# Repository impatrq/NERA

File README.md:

# N.E.R.A.

**Neuro Estimulación y Relajación Asistida**

Somos estudiantes de 7.º año de Aviónica de la **Escuela de Educación Secundaria Técnica N.º 7 «Taller Regional Quilmes» (IMPA)**. Durante 2026 desarrollamos NERA, un proyecto que combina investigación, electrónica, programación y diseño 3D.

[Repositorio oficial](https://github.com/impatrq/NERA) · [Seguimiento en Trello](https://trello.com/b/I9nTunkC/kanban-2026722cnera)

## ¿Qué es NERA?

NERA surgió con la idea de desarrollar una herramienta tecnológica que pueda acompañar a personas en situaciones de estrés o ansiedad. Construimos un prototipo portátil con **dos dispositivos principales: un reloj y una vincha**. Una aplicación móvil complementa el sistema y permite consultar las mediciones.

También investigamos los campos electromagnéticos pulsados (**PEMF**) de baja frecuencia y sus posibles aplicaciones. Esta parte sigue siendo experimental: todavía no demostramos efectos terapéuticos ni validamos la seguridad del dispositivo para su aplicación sobre personas.

## ¿Cómo funciona?

El **reloj** utiliza un ESP32-S3 para recopilar información de los sensores, procesarla y mostrarla en su pantalla táctil. Mediante **Bluetooth Low Energy (BLE)** envía lecturas a la aplicación móvil, donde se pueden consultar datos, historial y preferencias.

El reloj también se comunica con la **vincha**, controlada por un ESP32-C3, mediante **ESP-NOW**. Probamos el intercambio de mensajes, alertas de laboratorio y confirmaciones de recepción. La vincha contiene bobinas y una electrónica de control; el accionamiento seguro y automático de las bobinas a partir de las mediciones todavía requiere validación eléctrica.

## Prototipos reales

Estas son las versiones físicas del reloj y la vincha que construimos, ajustamos y presentamos durante el desarrollo del proyecto.

| Reloj NERA | Vincha NERA |
|:---:|:---:|
|  |  |
| **Reloj con carcasa impresa en 3D** | **Vincha con las carcasas de las bobinas** |

## Modelos actuales en CAD

Estos son algunos de los diseños actuales de la estructura del reloj y de la vincha hechos para adaptar el prototipo a los componentes reales.

| Modelo del reloj | Modelo de la vincha |
|:---:|:---:|
|  |  |
| **Carcasa del reloj** | **Soporte de la vincha y bobina** |

## PCB y proceso electrónico

Durante el proyecto diseñamos placas, corregimos pistas, soldamos componentes y probamos módulos reales para verificar conexiones y funcionamiento.

| Diseño PCB | Placa en pruebas |
|:---:|:---:|
|  |  |
| **Diseño de la PCB** | **Placa de sensores armada** |

## Componentes del sistema

### Reloj inteligente

El reloj utiliza un **ESP32-S3** con pantalla táctil de **240 × 320 píxeles**. El firmware se desarrolló con **C/C++, ESP-IDF, FreeRTOS y LVGL**.

| Componente | Función |
| --- | --- |
| **ESP32-S3** | Procesamiento, pantalla y comunicaciones inalámbricas. |
| **MAX30102** | Señal óptica para estimar frecuencia cardíaca y SpO₂. |
| **MLX90614** | Medición infrarroja de temperatura de objeto. |
| **MPU6050** | Registro de movimiento mediante acelerómetro y giroscopio. |

Las estimaciones de pulso y SpO₂ dependen de lecturas válidas. La temperatura infrarroja registrada no representa directamente la temperatura corporal central.

[Ver firmware del reloj](firmware/Codigo%20Reloj/) · [Guía técnica](firmware/Codigo%20Reloj/LEER_PRIMERO.md)

### Vincha experimental

La vincha incorpora un **ESP32-C3**, una placa controladora, una etapa de potencia y bobinas realizadas con cobre esmaltado. Diseñamos y fabricamos distintas versiones de las carcasas para montar los componentes.

Investigamos frecuencias entre **10 y 30 Hz**. El firmware publicado contiene una prueba de señal a **15 Hz con las bobinas desconectadas**. Esta prueba permite comprobar la salida eléctrica, pero no demuestra la seguridad ni la eficacia de la estimulación.

[Ver firmware de la vincha](firmware/Codigo%20Vincha/) · [Documentación de la prueba de 15 Hz](firmware/Codigo%20Vincha/docs/PRUEBA_GPIO5_15HZ.md)

### Aplicación móvil

La aplicación fue desarrollada con **Flutter y Dart**. Cuenta con las secciones **Inicio, Salud, Apoyo y Perfil**. Permite consultar mediciones e historial del reloj por BLE, configurar preferencias y utilizar funciones de respiración. La red de apoyo está contemplada en la interfaz; el envío automático de avisos a contactos todavía no se encuentra implementado.

[Ver aplicación](firmware/Codigo%20Aplicacion/) · [Mapa del código](firmware/Codigo%20Aplicacion/GUIA_CODIGO.md)

| Pantalla de inicio | Consulta de mediciones |
| :---: | :---: |
|  |  |
| **Inicio** | **Salud** |

## Presupuesto estimado

El costo estimado de los materiales electrónicos relevados es de **$156.978,12 ARS**. Son **precios de referencia**, no gastos efectivamente comprobados.

| Componente | Cantidad | Subtotal (ARS) |
| --- | :---: | ---: |
| ESP32-S3 + pantalla | 1 | $48.510 |
| ESP32-C3 SuperMini | 1 | $7.999 |
| MAX30102 | 1 | $7.860 |
| MLX90614 | 1 | $24.459 |
| MPU6050 | 1 | $6.149 |
| MOSFET IRFZ44N | 2 | $4.398 |
| TP4056 (módulo) | 1 | $3.499 |
| Baterías 18650 | 2 | $9.213,16 |
| Baterías LQ-S1 (pack de 2) | 1 | $14.418,97 |
| Cobre esmaltado (250 g) | 1 | $19.123,99 |
| LM2596 | 1 | $4.999 |
| Portabaterías | 1 | $6.349 |
| **Total estimado** |  | **$156.978,12** |

Este valor **no incluye** fabricación de PCB, resistencias, capacitores, diodos, cables, impresión 3D, tornillos ni otros materiales. Algunas cantidades fueron estimadas a partir de los circuitos y no está confirmado que se hayan comprado todos los elementos de la lista.

## Avances y estado actual

A lo largo del año fabricamos y probamos las placas y carcasas, desarrollamos la interfaz del reloj e integramos la aplicación. Las pruebas documentadas incluyen comunicación **BLE** entre el reloj y el teléfono, sincronización e historial de mediciones y comunicación **ESP-NOW** entre los dos microcontroladores.

El prototipo sigue en desarrollo. Quedan pendientes ajustes en la alimentación, estabilidad de sensores, validación del circuito de potencia y funcionamiento integrado. La activación mediante combinación de variables es una idea de evolución del sistema; en el firmware documentado actualmente se usan reglas de laboratorio independientes para pulso y temperatura. **NERA no es un sistema médico validado para diagnosticar o tratar estrés o ansiedad.**

## Integrantes

| Integrante | Área principal |
| --- | --- |
| **Erik Kriznjak** | Programación del reloj, aplicación móvil, comunicaciones e integración. |
| **Juan Cruz Beneitez** | Electrónica, sensores, PCB, soldadura y pruebas de los circuitos. |
| **Ignacio Villegas** | Diseño CAD, impresión 3D, carcasas y armado de los dispositivos. |
| **Enzo Segovia** | Investigación de componentes, parámetros fisiológicos y tecnología PEMF. |

Los cuatro participamos en las pruebas, correcciones y exposición del prototipo.

## Archivos del proyecto

| Carpeta | Contenido |
| --- | --- |
| [`circuitos/`](circuitos/) | Esquemáticos y diseños de placas PCB. |
| [`mechanical/`](mechanical/) | Modelos 3D, carcasas y archivos STL de fabricación. |
| [`firmware/`](firmware/) | Código del reloj, la vincha y la aplicación móvil. |
| [`docs/`](docs/) | Manuales, documentación técnica e imágenes. |

Para acceder al código y a sus instrucciones de compilación: [README de firmware](firmware/README.md).

---

**Proyecto NERA · 7.º año de Aviónica · E.E.S.T. N.º 7 · Quilmes · 2026**

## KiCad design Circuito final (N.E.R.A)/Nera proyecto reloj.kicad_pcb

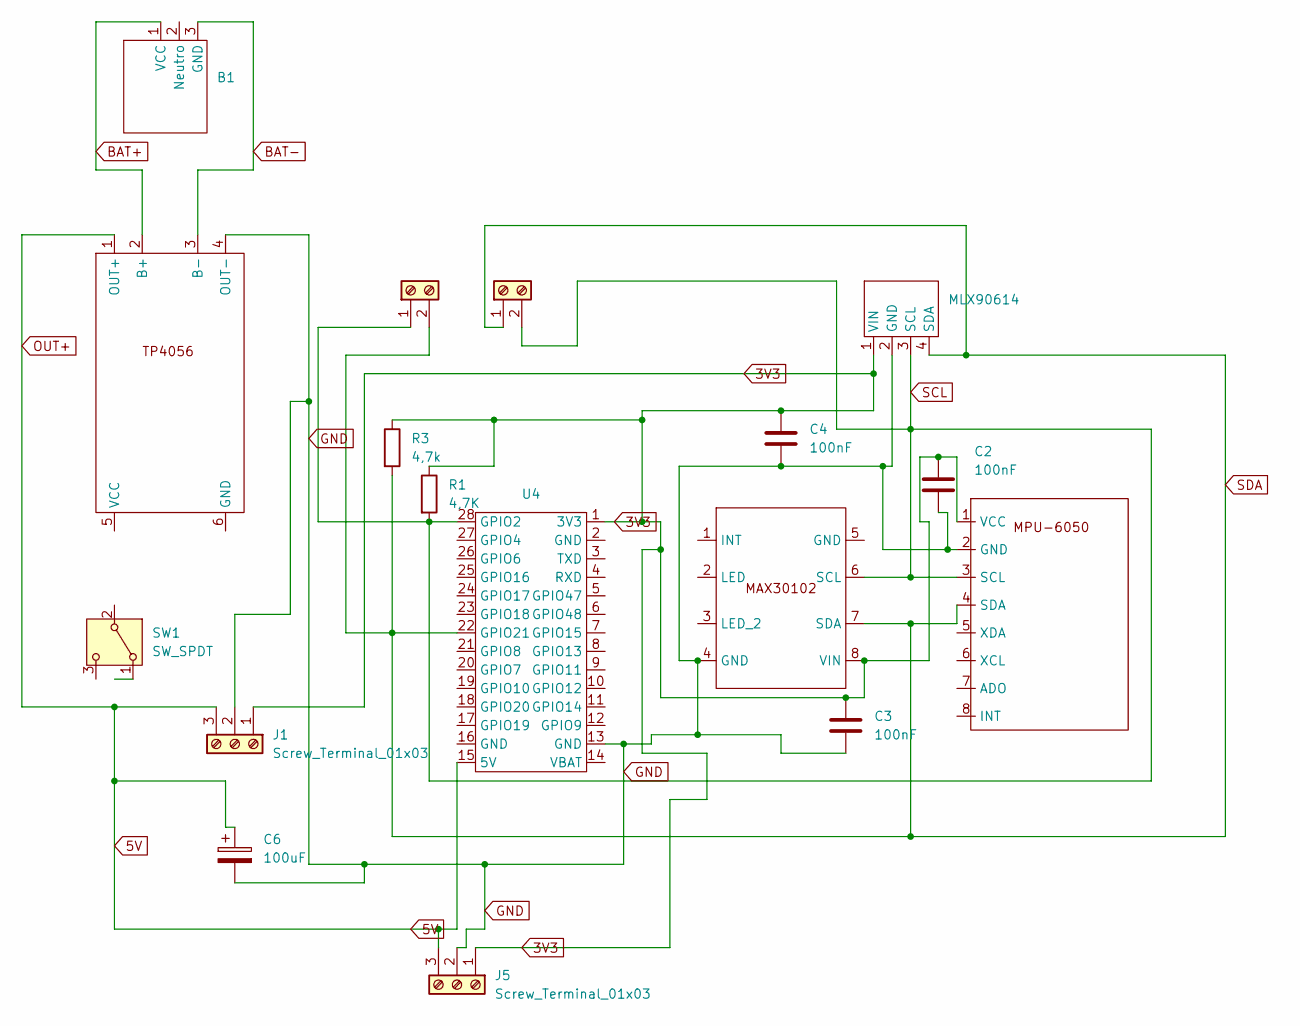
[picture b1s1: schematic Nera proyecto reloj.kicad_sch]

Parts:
B1: batman 51
C2, C3, C4: 100nF; C_Radial_D4.0mm_H5.0mm_P1.50mm
C6: 100uF; CP_Radial_D5.0mm_P2.00mm
J1, J5: Screw_Terminal_01x03; TerminalBlock_MaiXu_MX126-5.0-03P_1x03_P5.00mm
J3: TerminalBlock:TerminalBlock_MaiXu_MX126-5.0-02P_1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; TerminalBlock_MaiXu_MX126-5.0-02P_1x02_P5.00mm
J4: Screw_Terminal_01x02; TerminalBlock_MaiXu_MX126-5.0-02P_1x02_P5.00mm
MLX90614: MLX90614
Max1: MAX30102; Max 30102
R1: 4,7K; R_Axial_DIN0411_L9.9mm_D3.6mm_P15.24mm_Horizontal
R3: 4,7k; R_Axial_DIN0411_L9.9mm_D3.6mm_P15.24mm_Horizontal
SW1: SW_SPDT; SW_Slide_SPDT_Straight_CK_OS102011MS2Q
TP1: TP4056-42-ESOP8; Modulito
U2: MPU-6050; MPU 6050
U4: esp32 s3

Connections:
3V3: C2.1, C3.1, C4.1, J1.1, J5.1, MLX90614.1 (VIN), Max1.8 (VIN), R1.1, R3.1, U2.1 (VCC), U4.1 (3V3)
5V: C6.1, J1.3, J5.3, TP1.1 (OUT+), U4.15 (5V)
BAT+: B1.1 (VCC), TP1.2 (B+)
BAT-: B1.3 (GND), TP1.3 (B-)
GND: C2.2, C3.2, C4.2, C6.2, J1.2, J5.2, MLX90614.2 (GND), Max1.4 (GND), TP1.4 (OUT-), U2.2 (GND), U4.13 (GND)
SCL: J3.1, J4.2, MLX90614.3 (SCL), Max1.6 (SCL), R1.2, U2.3 (SCL), U4.28 (GPIO2)
SDA: J3.2, J4.1, MLX90614.4 (SDA), Max1.7 (SDA), R3.2, U2.4 (SDA), U4.22 (GPIO21)

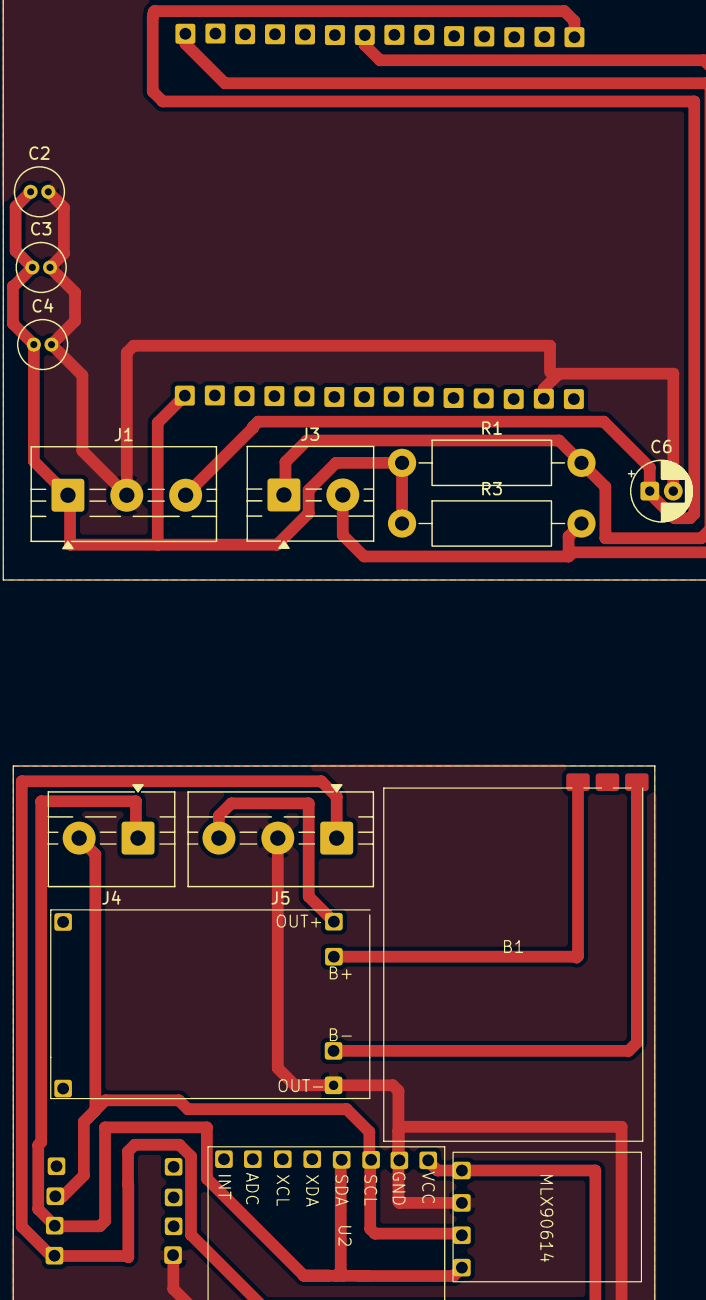
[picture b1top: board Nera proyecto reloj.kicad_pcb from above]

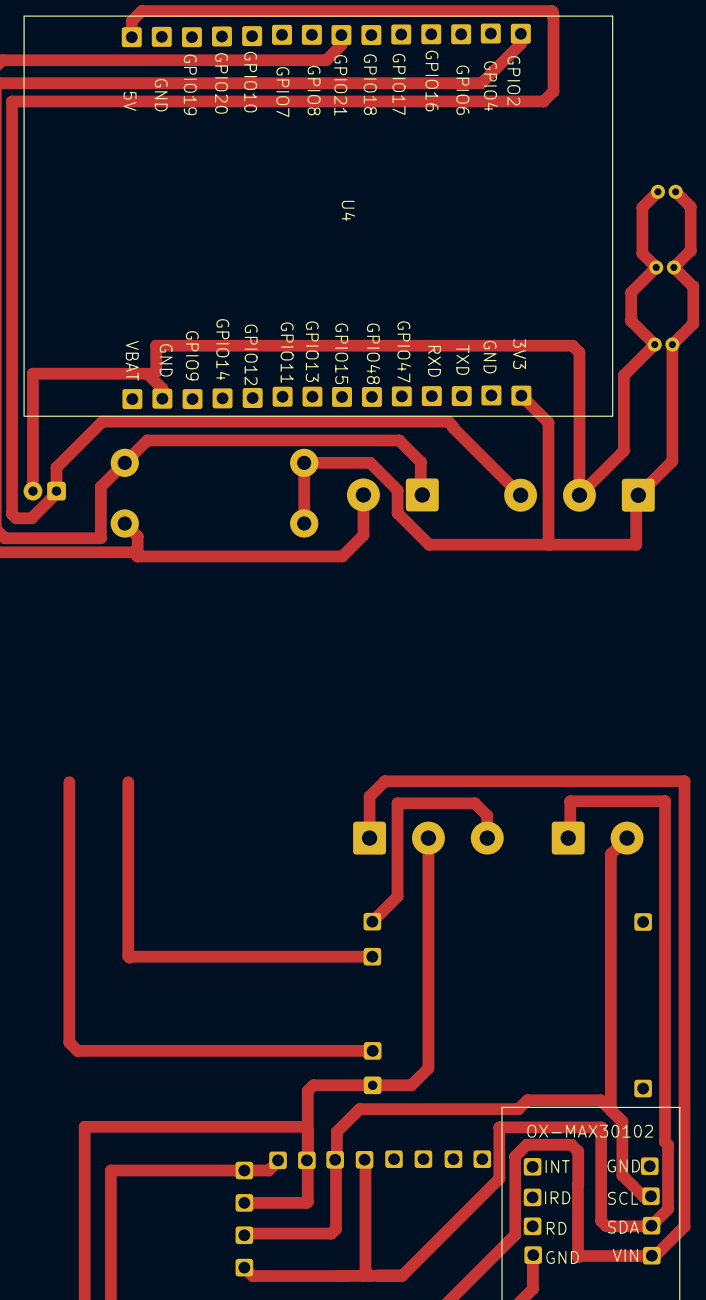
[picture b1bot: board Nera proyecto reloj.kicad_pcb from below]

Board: 2 copper layers, 16 parts (2 on the bottom side), 7 nets.

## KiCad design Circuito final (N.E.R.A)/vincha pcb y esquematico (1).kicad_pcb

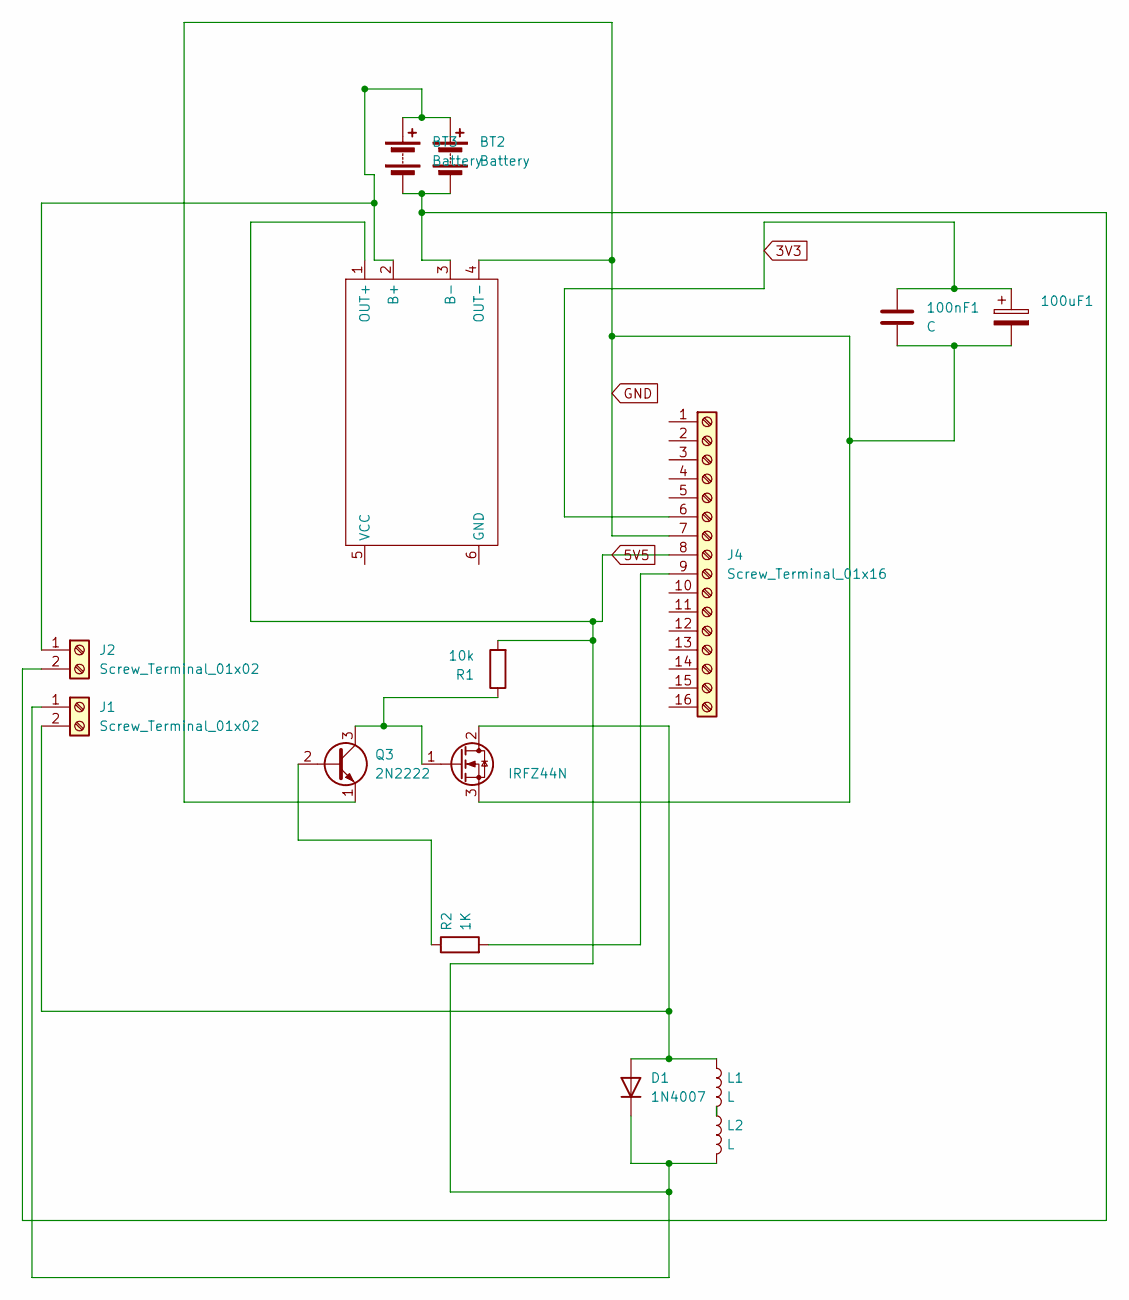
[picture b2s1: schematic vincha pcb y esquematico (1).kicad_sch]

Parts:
100nF1: C; C_0805_2012Metric
100uF1: 100uF; CP_Radial_D10.0mm_P3.80mm
BT2, BT3: Battery; bateria escopeta
D1: 1N4007; D_DO-41_SOD81_P10.16mm_Horizontal
J1, J2: Screw_Terminal_01x02; TerminalBlock_MaiXu_MX126-5.0-02P_1x02_P5.00mm
J4: Screw_Terminal_01x16; Nera (2)
L1: L; BOBINA_PEMF_VINCHA 1
L2: L; BOBINA_PEMF_VINCHA2
Q2: IRFZ44N; TO-220-3_Vertical
Q3: 2N2222; TO-92
R1: 10k; R_Axial_DIN0411_L9.9mm_D3.6mm_P15.24mm_Horizontal
R2: 1K; R_Axial_DIN0411_L9.9mm_D3.6mm_P15.24mm_Horizontal
U1: Modulo_de_carga; Modulito

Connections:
3V3: 100nF1.1, 100uF1.1, J4.6
5V5: D1.1 (K), J1.1, J4.8, L2.2, R1.2, U1.1 (OUT+)
GND: 100nF1.2, 100uF1.2, J4.7, Q2.3 (S), Q3.1 (E), U1.4 (OUT-)
unnamed: BT2.1 (+), BT3.1 (+), J2.1, U1.2 (B+)
unnamed: BT2.2 (-), BT3.2 (-), J2.2, U1.3 (B-)
unnamed: D1.2 (A), J1.2, L1.1, Q2.2 (D)
unnamed: J4.9, R2.2
unnamed: L1.2, L2.1
unnamed: Q2.1 (G), Q3.3 (C), R1.1
unnamed: Q3.2 (B), R2.1

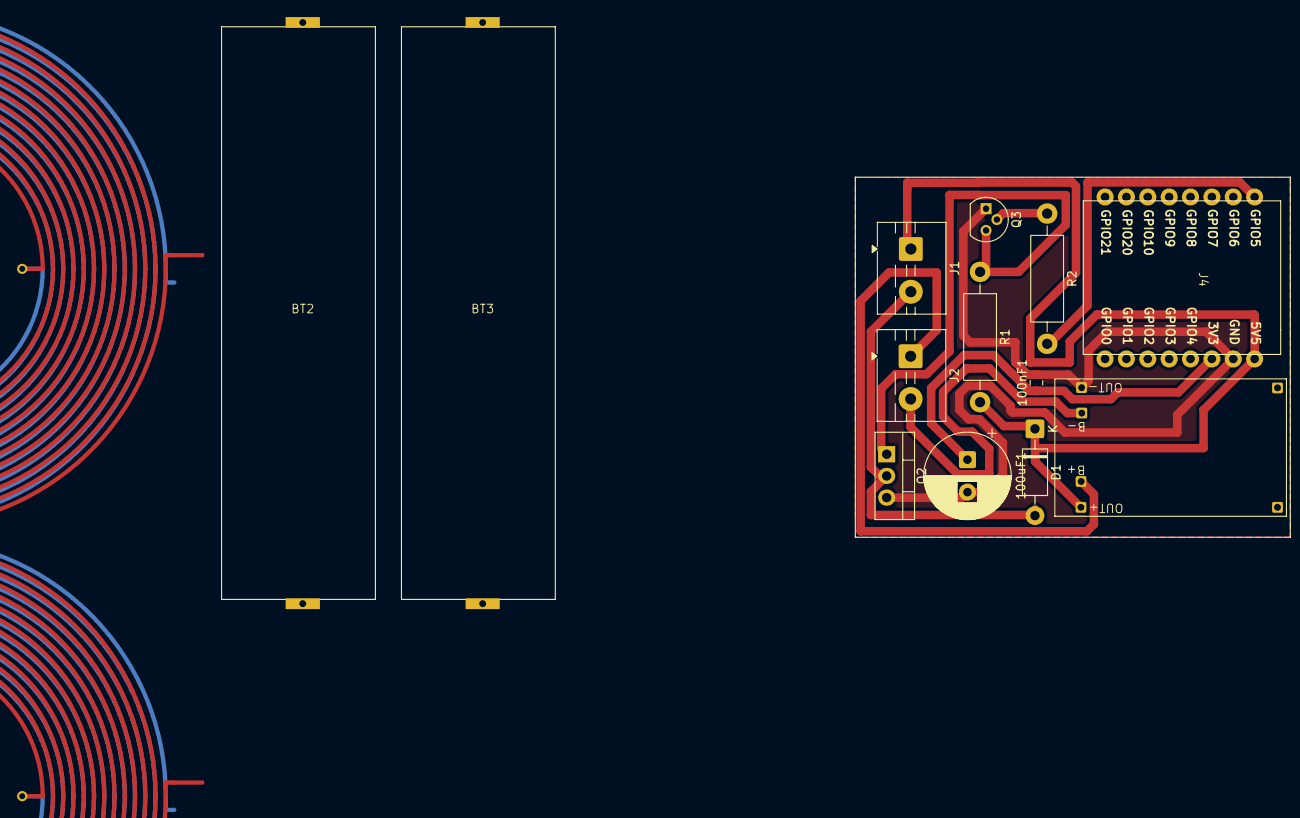
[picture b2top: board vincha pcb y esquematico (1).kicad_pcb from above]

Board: 2 copper layers, 15 parts (0 on the bottom side), 10 nets.

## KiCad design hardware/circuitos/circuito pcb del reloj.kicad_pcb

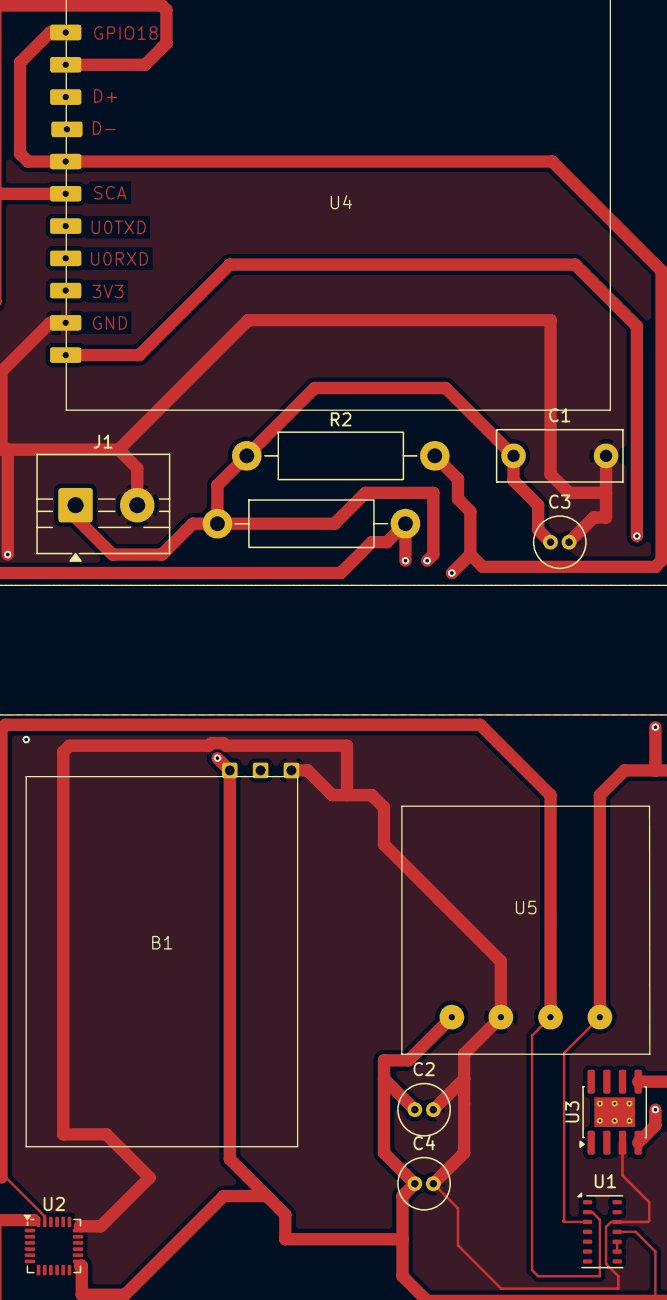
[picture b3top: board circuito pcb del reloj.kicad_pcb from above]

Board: 2 copper layers, 13 parts (0 on the bottom side), 6 nets.

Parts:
B1: batman 51
C1: 10uF; C_Rect_L10.0mm_W4.0mm_P7.50mm_FKS3_FKP3
C2, C3, C4: 100nF; C_Radial_D4.0mm_H5.0mm_P1.50mm
J1: Screw_Terminal_01x02; TerminalBlock_MaiXu_MX126-5.0-02P_1x02_P5.00mm
R1, R2: 4,7K; R_Axial_DIN0411_L9.9mm_D3.6mm_P15.24mm_Horizontal
U1: MAX30102; Maxim_OLGA-14_3.3x5.6mm_P0.8mm
U2: MPU-6050; InvenSense_QFN-24_4x4mm_P0.5mm
U3: TP4056-42-ESOP8; SOIC-8-1EP_3.9x4.9mm_P1.27mm_EP2.41x3.3mm_ThermalVias
U4: ESP32_C6
U5: Tito

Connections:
5v: U3.4 (V_{CC}), U4.11 (5V)
unnamed: U1.9 (VLED+), U1.10 (VLED+)
clock: R2.2, U1.2 (SCL), U2.23 (SCL), U4.1 (GPIO18), U4.5 (SCL), U5.3 (SCL)
dat sensor: R1.2, U1.3 (SDA), U2.24 (SDA), U4.2 (GPIO9), U4.6 (SDA), U5.4 (SDA)
prime: B1.1 (VCC), C1.1, C2.1, C3.1, C4.1, J1.1, R1.1, R2.1, U1.11 (VDD), U2.13 (VDD), U3.5 (BAT), U5.1 (VIN)
tierra: B1.3 (GND), C1.2, C2.2, C3.2, C4.2, J1.2, U1.12 (GND), U2.18 (GND), U3.3 (GND), U4.10 (GND), U5.2 (GND)

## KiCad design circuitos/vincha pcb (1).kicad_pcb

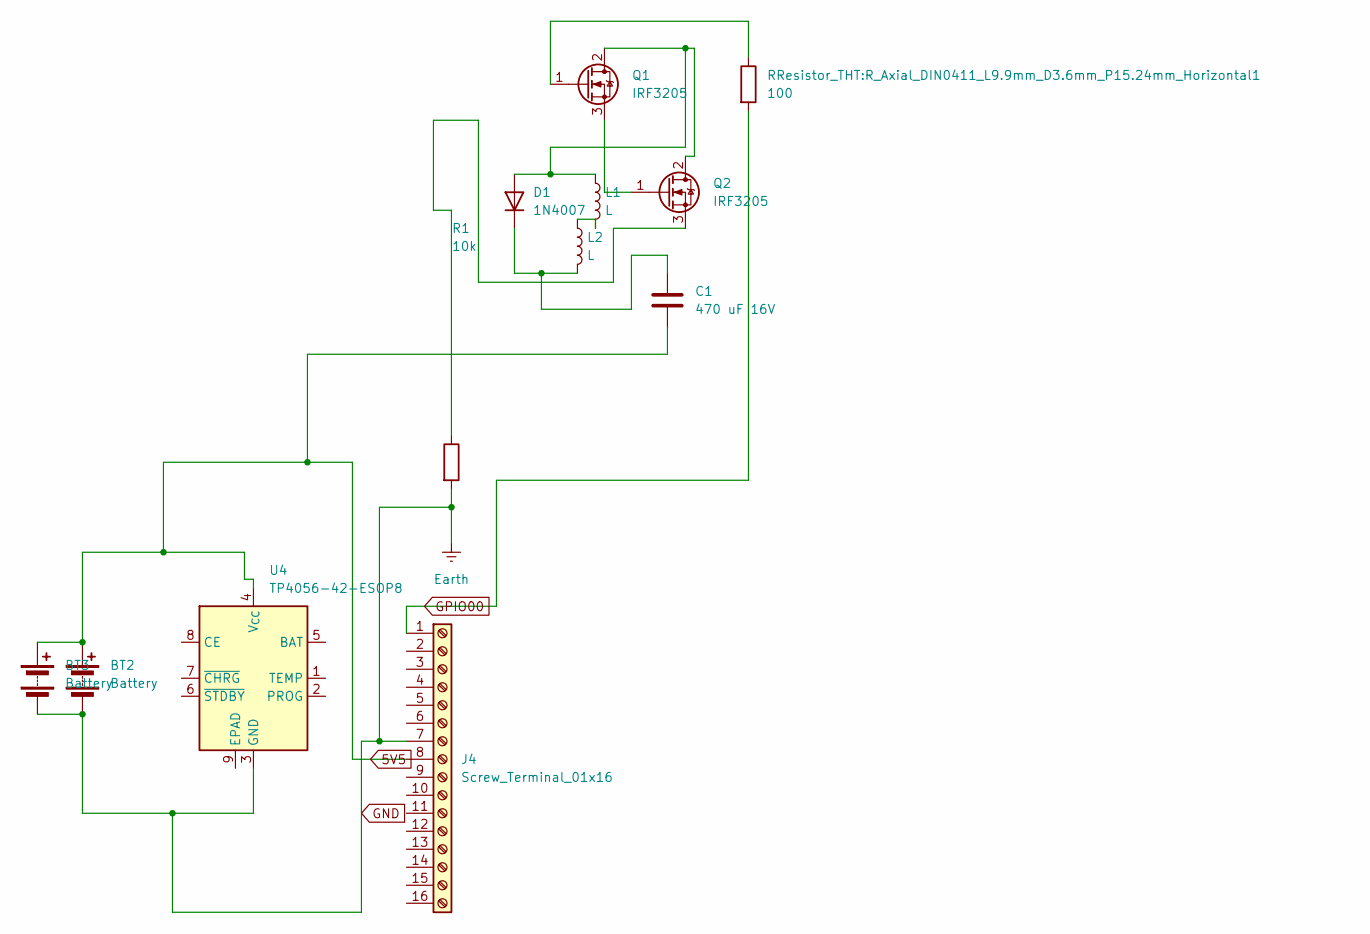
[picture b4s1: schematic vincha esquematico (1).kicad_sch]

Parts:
BT2, BT3: Battery; bateria escopeta
C1: 470 uF 16V; CP_EIA-6032-15_Kemet-U
D1: 1N4007; D_DO-41_SOD81_P10.16mm_Horizontal
J4: Screw_Terminal_01x16; Nera (2)
L1, L2: L; inductor pemf
Q1, Q2: IRF3205; TO-220-3_Vertical
R1: 10k; R_Axial_DIN0411_L9.9mm_D3.6mm_P15.24mm_Horizontal
RResistor_THT:R_Axial_DIN0411_L9.9mm_D3.6mm_P15.24mm_Horizontal1: 100; R_Axial_DIN0411_L9.9mm_D3.6mm_P15.24mm_Horizontal
U4: TP4056-42-ESOP8; SOIC-8-1EP_3.9x4.9mm_P1.27mm_EP2.41x3.3mm_ThermalVias

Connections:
5V5: BT2.1 (+), BT3.1 (+), C1.2, J4.8, U4.4 (V_{CC})
GND: BT2.2 (-), BT3.2 (-), J4.7, R1.2, U4.3 (GND)
GPIO00: J4.1, RResistor_THT:R_Axial_DIN0411_L9.9mm_D3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.2
unnamed: D1.2 (A), L1.1, Q1.2 (D), Q2.2 (D)
unnamed: C1.1, D1.1 (K), L2.2
unnamed: L1.2, L2.1
unnamed: Q1.1 (G), RResistor_THT:R_Axial_DIN0411_L9.9mm_D3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.1
unnamed: Q1.3 (S), Q2.1 (G)
unnamed: Q2.3 (S), R1.1

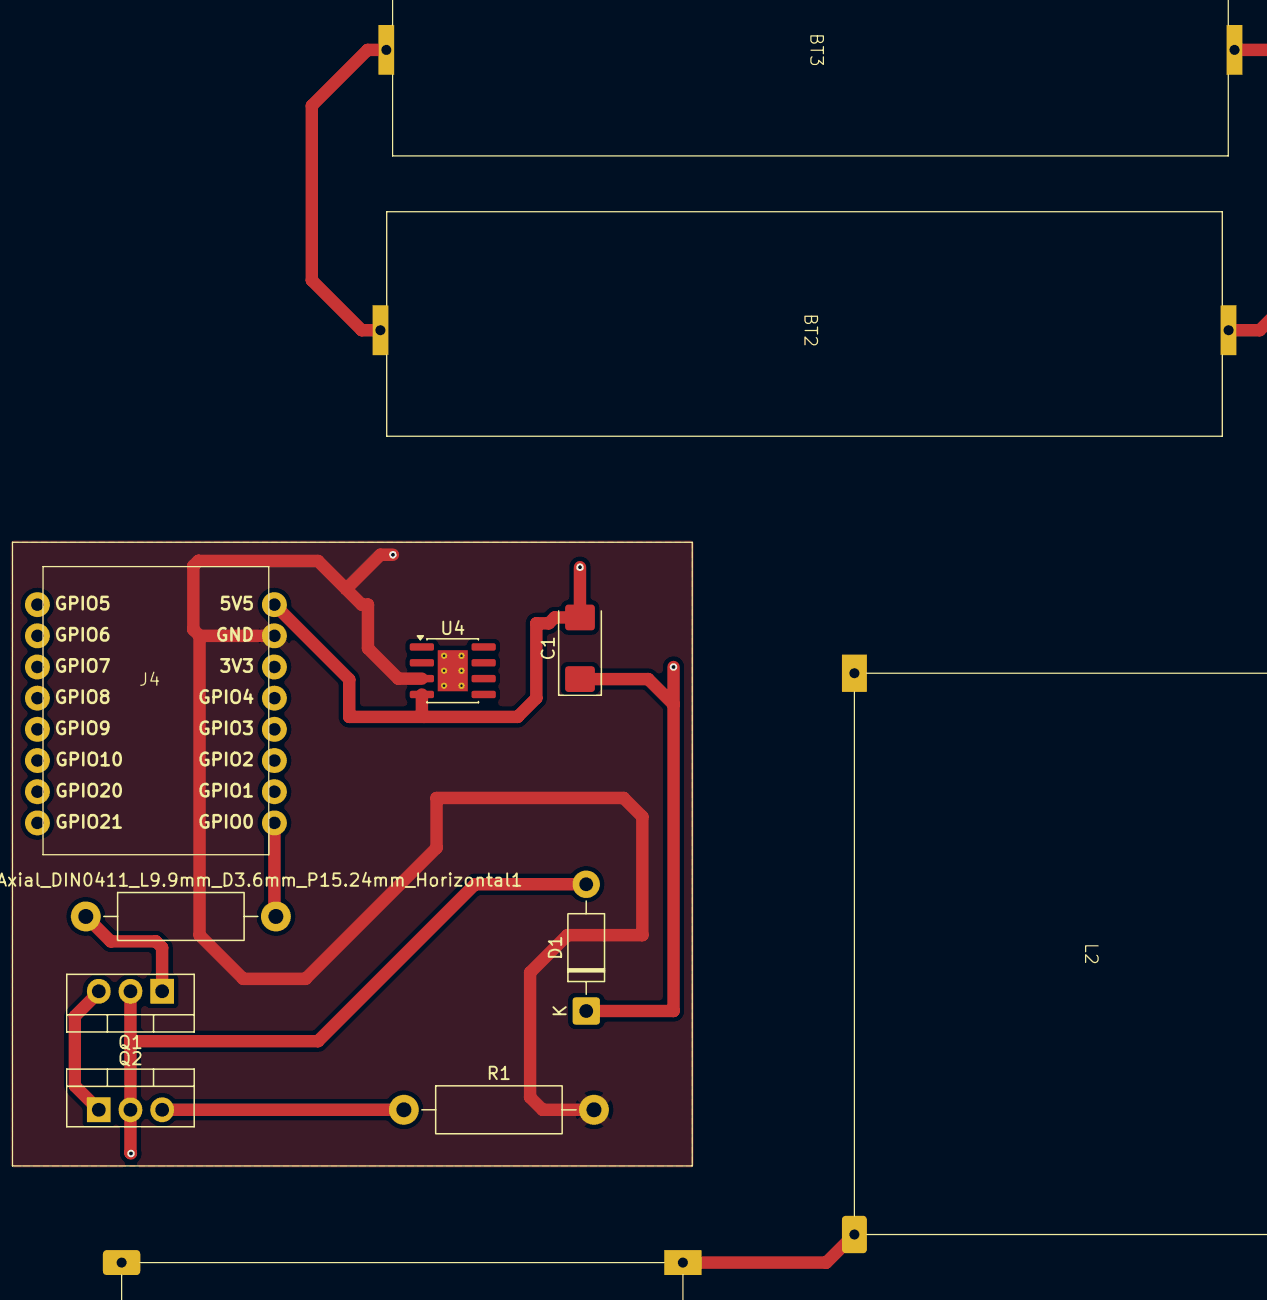
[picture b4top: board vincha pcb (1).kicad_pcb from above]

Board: 2 copper layers, 12 parts (0 on the bottom side), 9 nets.

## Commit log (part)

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2026-05-14 Anteproyecto
2026-06-23 Imagenes de la App
    Primeras imagenes de como se ve la app
